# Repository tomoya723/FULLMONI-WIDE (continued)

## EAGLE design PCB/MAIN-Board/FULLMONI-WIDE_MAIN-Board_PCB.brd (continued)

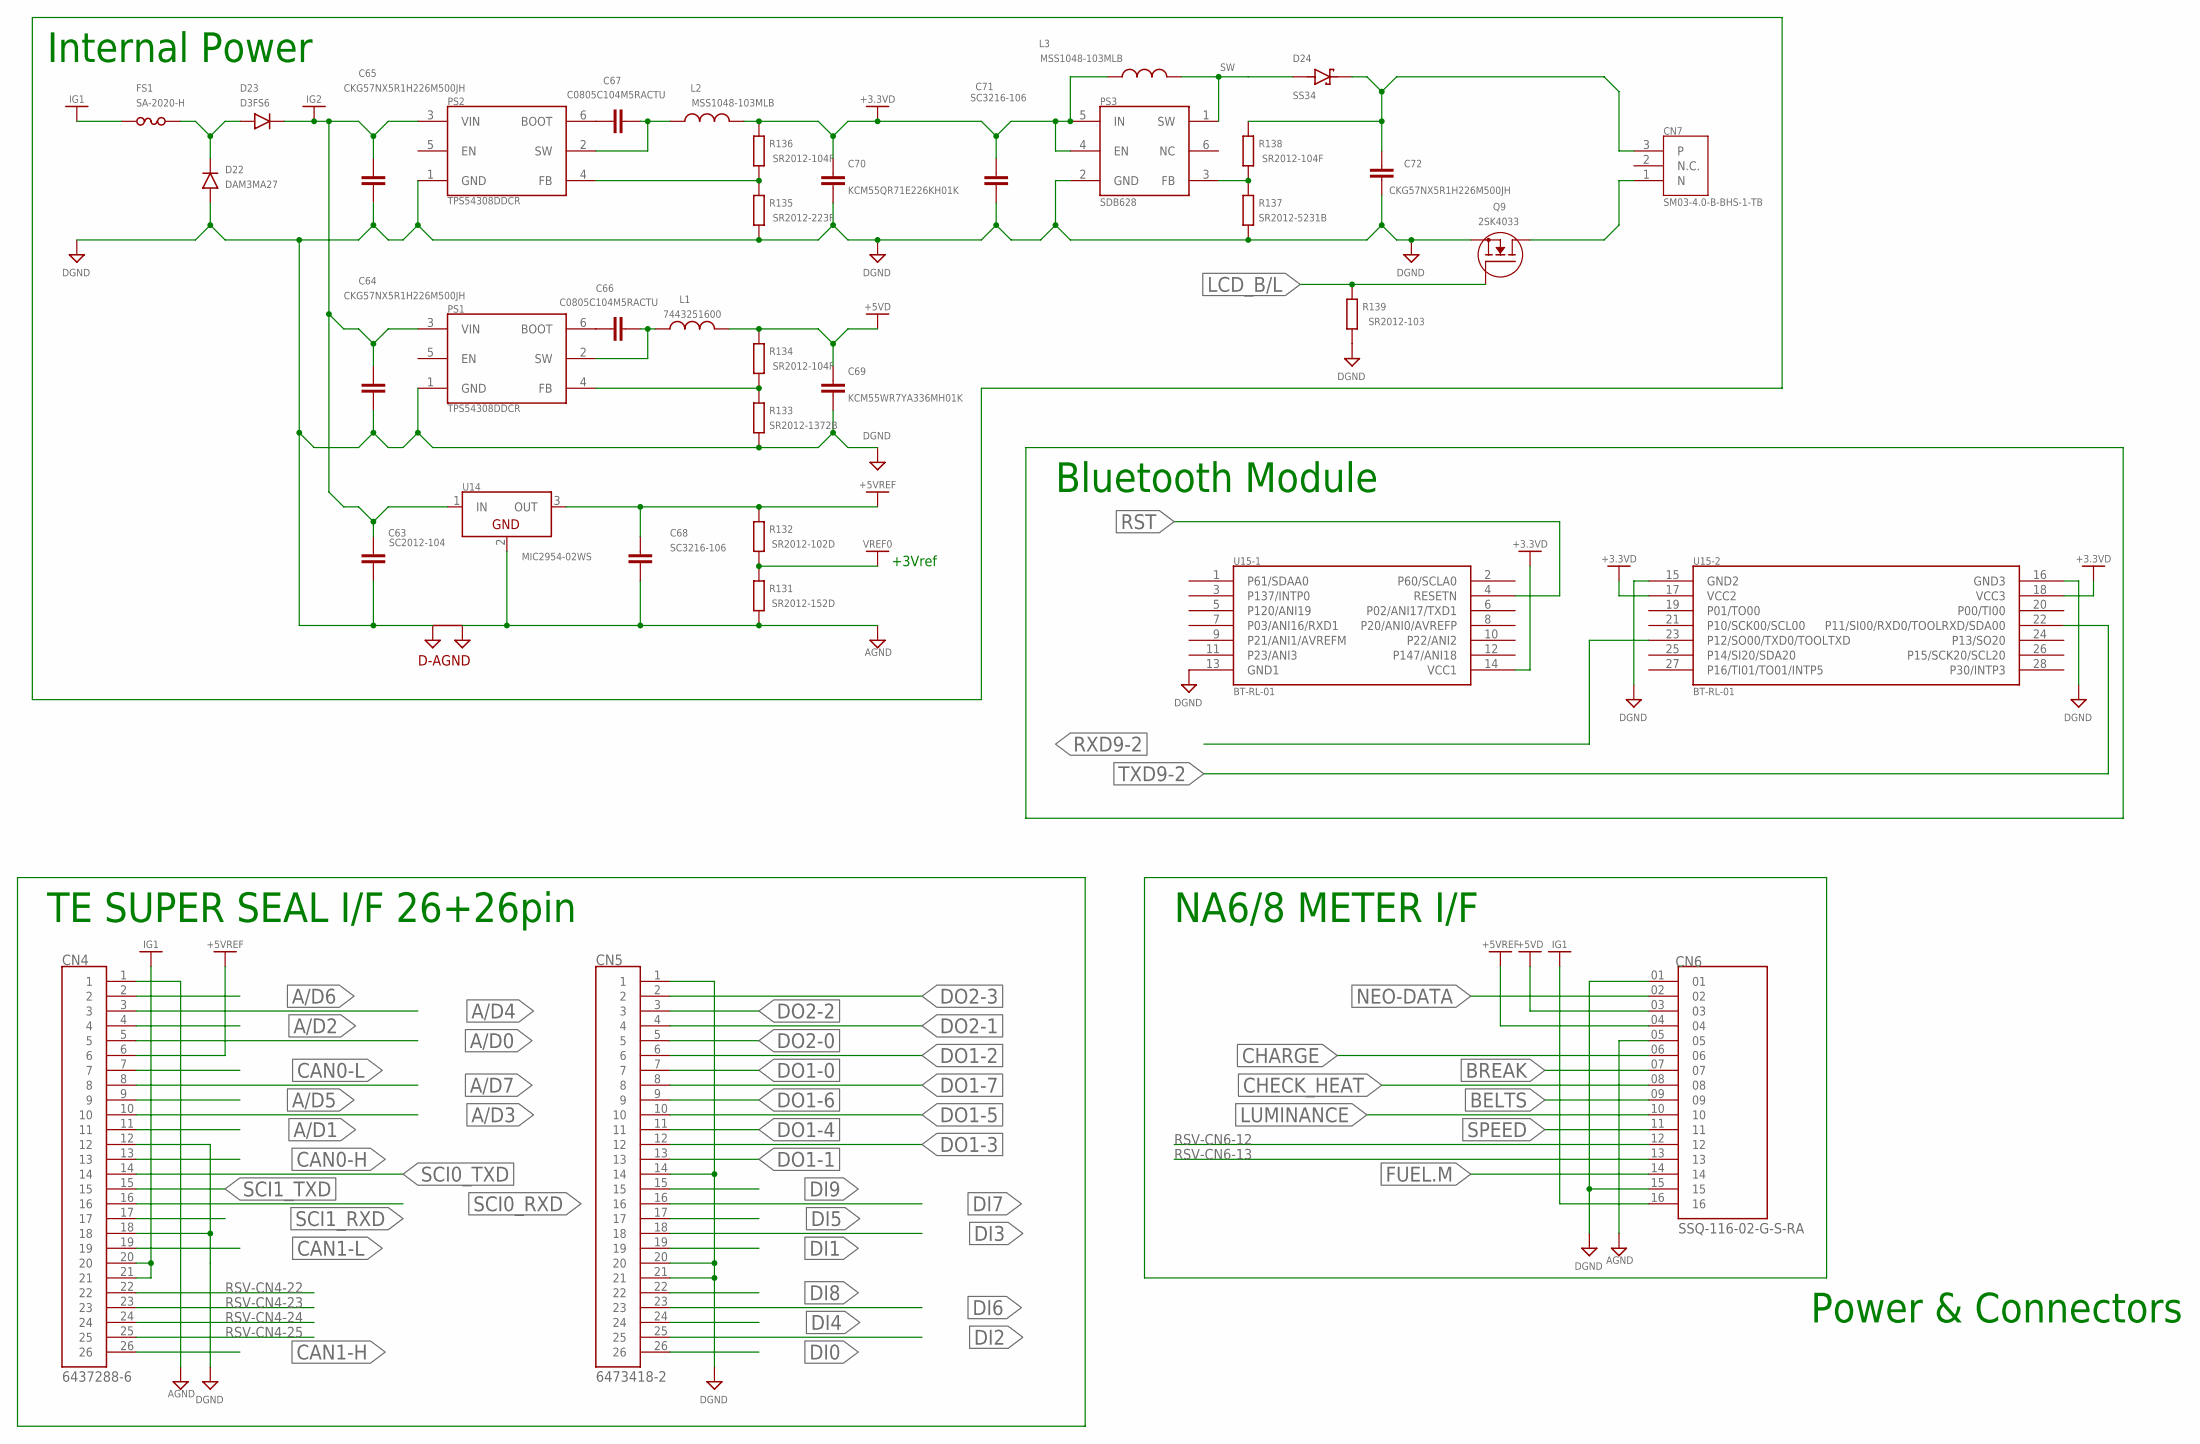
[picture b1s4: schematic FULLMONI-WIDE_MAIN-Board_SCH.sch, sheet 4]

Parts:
$4_490_$_2024-03-09_15-35-59: D-AGND
C63: SC2012-104; CAPC2012X110
C64, C65, C72: CKG57NX5R1H226M500JH
C66, C67: C0805C104M5RACTU; CAPC2012X110
C68, C71: SC3216-106; CAPC3216X135
C69: KCM55WR7YA336MH01K; KCM55QR71E226KH01K
C70: KCM55QR71E226KH01K
CN4: 6437288-6; TE_6437288-6
CN5: 6473418-2; TE_6473418-2
CN6: SSQ-116-02-G-S-RA; SAMTEC_SSQ-116-02-G-S-RA
CN7: SM03-4.0-B-BHS-1-TB
D22: DAM3MA27
D23: D3FS6
D24: SS34; DIOM6859X262N
FS1: SA-2020-H
L1: 7443251600; MSS1048-103MLB
L2, L3: MSS1048-103MLB
PS1, PS2: TPS54308DDCR; DBV_R-PDSO-G6
PS3: SDB628; TSOT23-6_DDC
Q9: 2SK4033; RJF0604JPD
R131: SR2012-152D; RESC2012X65
R132: SR2012-102D; RESC2012X65
R133: SR2012-1372B; RESC2012X65
R134, R136, R138: SR2012-104F; RESC2012X65
R135: SR2012-223F; RESC2012X65
R137: SR2012-5231B; RESC2012X65
R139: SR2012-103; RESC2012X65
U14: MIC2954-02WS
U15: BT-RL-01

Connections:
+3.3VD: C70.P$1, C71.1, L2.P$2 (2), L3.P$1 (1), PS3.4 (EN), PS3.5 (IN), R136.2, U15.14 (VCC1), U15.17 (VCC2), U15.18 (VCC3); also elsewhere on the board
+5VD: C69.P$1, CN6.03, L1.P$2 (2), R134.2; also elsewhere on the board
+5VREF: C68.1, CN4.6, CN6.04, R132.2, U14.3 (OUT); also elsewhere on the board
A/D0: CN4.5; also elsewhere on the board
A/D1: CN4.11; also elsewhere on the board
A/D2: CN4.4; also elsewhere on the board
A/D3: CN4.10; also elsewhere on the board
A/D4: CN4.3; also elsewhere on the board
A/D5: CN4.9; also elsewhere on the board
A/D6: CN4.2; also elsewhere on the board
A/D7: CN4.8; also elsewhere on the board
AGND: $4_490_$_2024-03-09_15-35-59.2 (AGND), C68.2, CN4.1, CN6.05, R131.1, U14.2 (GND); also elsewhere on the board
BELTS: CN6.09; also elsewhere on the board
BREAK: CN6.07; also elsewhere on the board
CAN0-H: CN4.13; also elsewhere on the board
CAN0-L: CN4.7; also elsewhere on the board
CAN1-H: CN4.26; also elsewhere on the board
CAN1-L: CN4.19; also elsewhere on the board
CHARGE: CN6.06; also elsewhere on the board
CHECK_HEAT: CN6.08; also elsewhere on the board
DGND: $4_490_$_2024-03-09_15-35-59.1 (DGND), C63.2, C64.P$2, C65.P$2, C69.P$2, C70.P$2, C71.2, C72.P$1, CN4.12, CN4.18, CN5.1, CN5.14, CN5.20, CN5.21, CN6.01, CN6.15, D22.P$1, PS1.1 (GND), PS2.1 (GND), PS3.2 (GND), Q9.3 (S), R133.1, R135.1, R137.1, R139.1, U15.13 (GND1), U15.15 (GND2), U15.16 (GND3); also elsewhere on the board
DI0: CN5.26; also elsewhere on the board
DI1: CN5.19; also elsewhere on the board
DI2: CN5.25; also elsewhere on the board
DI3: CN5.18; also elsewhere on the board
DI4: CN5.24; also elsewhere on the board
DI5: CN5.17; also elsewhere on the board
DI6: CN5.23; also elsewhere on the board
DI7: CN5.16; also elsewhere on the board
DI8: CN5.22; also elsewhere on the board
DI9: CN5.15; also elsewhere on the board
DO1-0: CN5.7; also elsewhere on the board
DO1-1: CN5.13; also elsewhere on the board
DO1-2: CN5.6; also elsewhere on the board
DO1-3: CN5.12; also elsewhere on the board
DO1-4: CN5.11; also elsewhere on the board
DO1-5: CN5.10; also elsewhere on the board
DO1-6: CN5.9; also elsewhere on the board
DO1-7: CN5.8; also elsewhere on the board
DO2-0: CN5.5; also elsewhere on the board
DO2-1: CN5.4; also elsewhere on the board
DO2-2: CN5.3; also elsewhere on the board
DO2-3: CN5.2; also elsewhere on the board
FUEL.M: CN6.14; also elsewhere on the board
IG1: CN4.20, CN4.21, CN6.16, FS1.2; also elsewhere on the board
IG2: C63.1, C64.P$1, C65.P$1, D23.P$2, PS1.3 (VIN), PS2.3 (VIN), U14.1 (IN)
LCD-A: C72.P$2, CN7.3, D24.C (K), R138.2
LCD-K: CN7.1 (N), Q9.4 (D)
LCD_B/L: Q9.1 (G), R139.2; also elsewhere on the board
LUMINANCE: CN6.10; also elsewhere on the board
unnamed: D22.P$2, D23.P$1, FS1.1
unnamed: C67.2, PS2.6 (BOOT)
unnamed: C66.2, PS1.6 (BOOT)
unnamed: C67.1, L2.P$1 (1), PS2.2 (SW)
unnamed: C66.1, L1.P$1 (1), PS1.2 (SW)
unnamed: PS2.4 (FB), R135.2, R136.1
unnamed: PS1.4 (FB), R133.2, R134.1
unnamed: PS3.3 (FB), R137.2, R138.1
NEO-DATA: CN6.02; also elsewhere on the board
RST: U15.4 (RESETN); also elsewhere on the board
RSV-CN4-22: CN4.22
RSV-CN4-23: CN4.23
RSV-CN4-24: CN4.24
RSV-CN4-25: CN4.25
RSV-CN6-12: CN6.12
RSV-CN6-13: CN6.13
RXD9-2: U15.23 (P12/SO00/TXD0/TOOLTXD); also elsewhere on the board
SCI0_RXD: CN4.16; also elsewhere on the board
SCI0_TXD: CN4.14; also elsewhere on the board
SCI1_RXD: CN4.17; also elsewhere on the board
SCI1_TXD: CN4.15; also elsewhere on the board
SPEED: CN6.11; also elsewhere on the board
SW: D24.A, L3.P$2 (2), PS3.1 (SW)
TXD9-2: U15.22 (P11/SI00/RXD0/TOOLRXD/SDA00); also elsewhere on the board
VREF0: R131.2, R132.1; also elsewhere on the board

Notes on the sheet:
Power & Connectors
+3Vref
TE SUPER SEAL I/F 26+26pin
NA6/8 METER I/F
Internal Power
Bluetooth Module

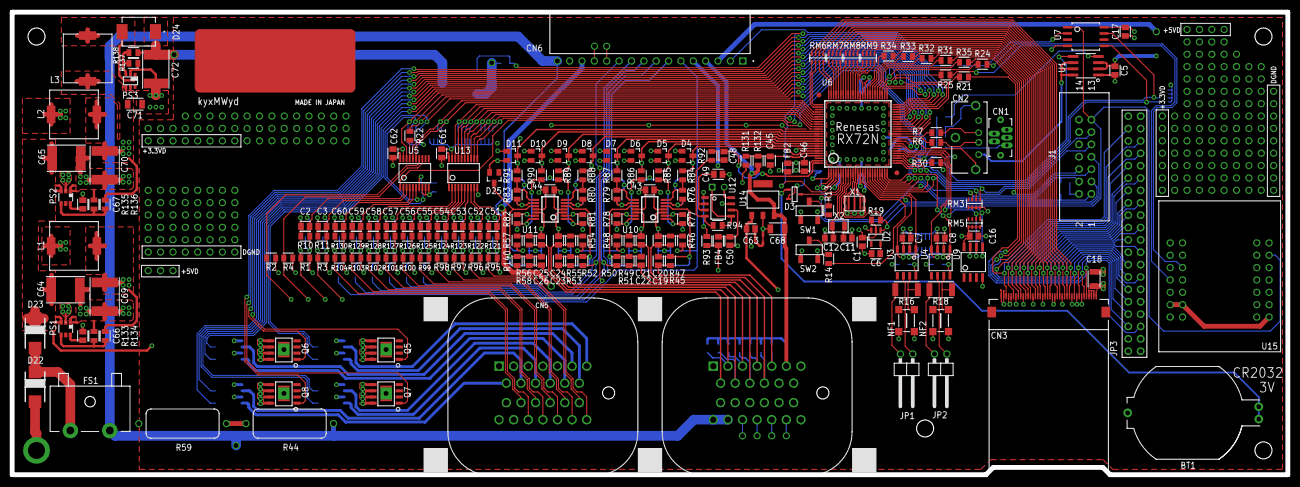
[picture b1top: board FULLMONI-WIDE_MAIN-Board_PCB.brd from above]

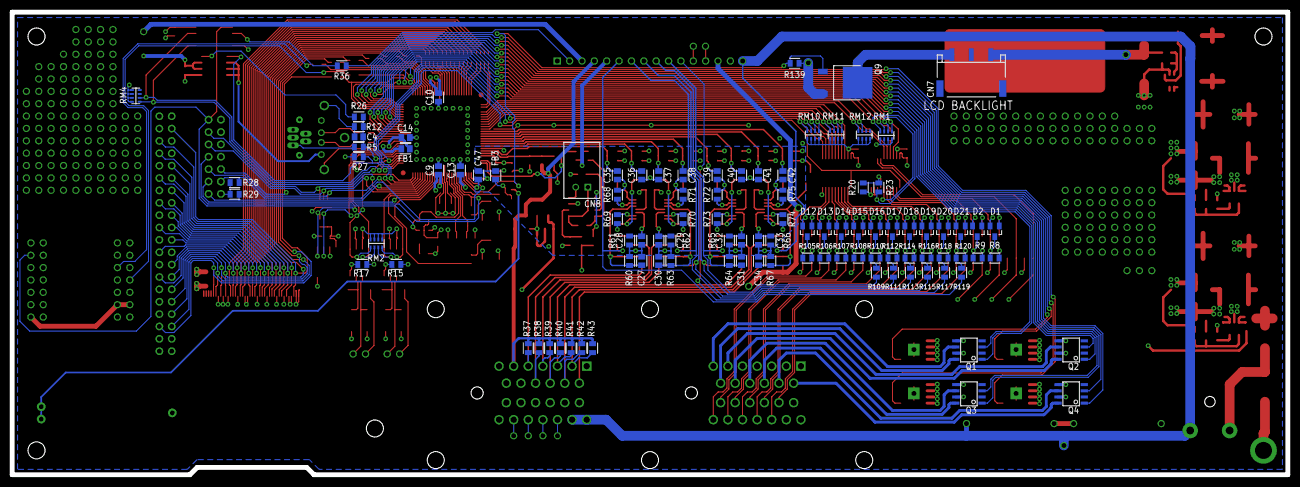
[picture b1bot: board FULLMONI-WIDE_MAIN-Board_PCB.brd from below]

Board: 4 copper layers, 262.0 x 95.0 mm, 303 parts (102 on the bottom side), 242 nets.

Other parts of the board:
U$2: FM-LOGO2

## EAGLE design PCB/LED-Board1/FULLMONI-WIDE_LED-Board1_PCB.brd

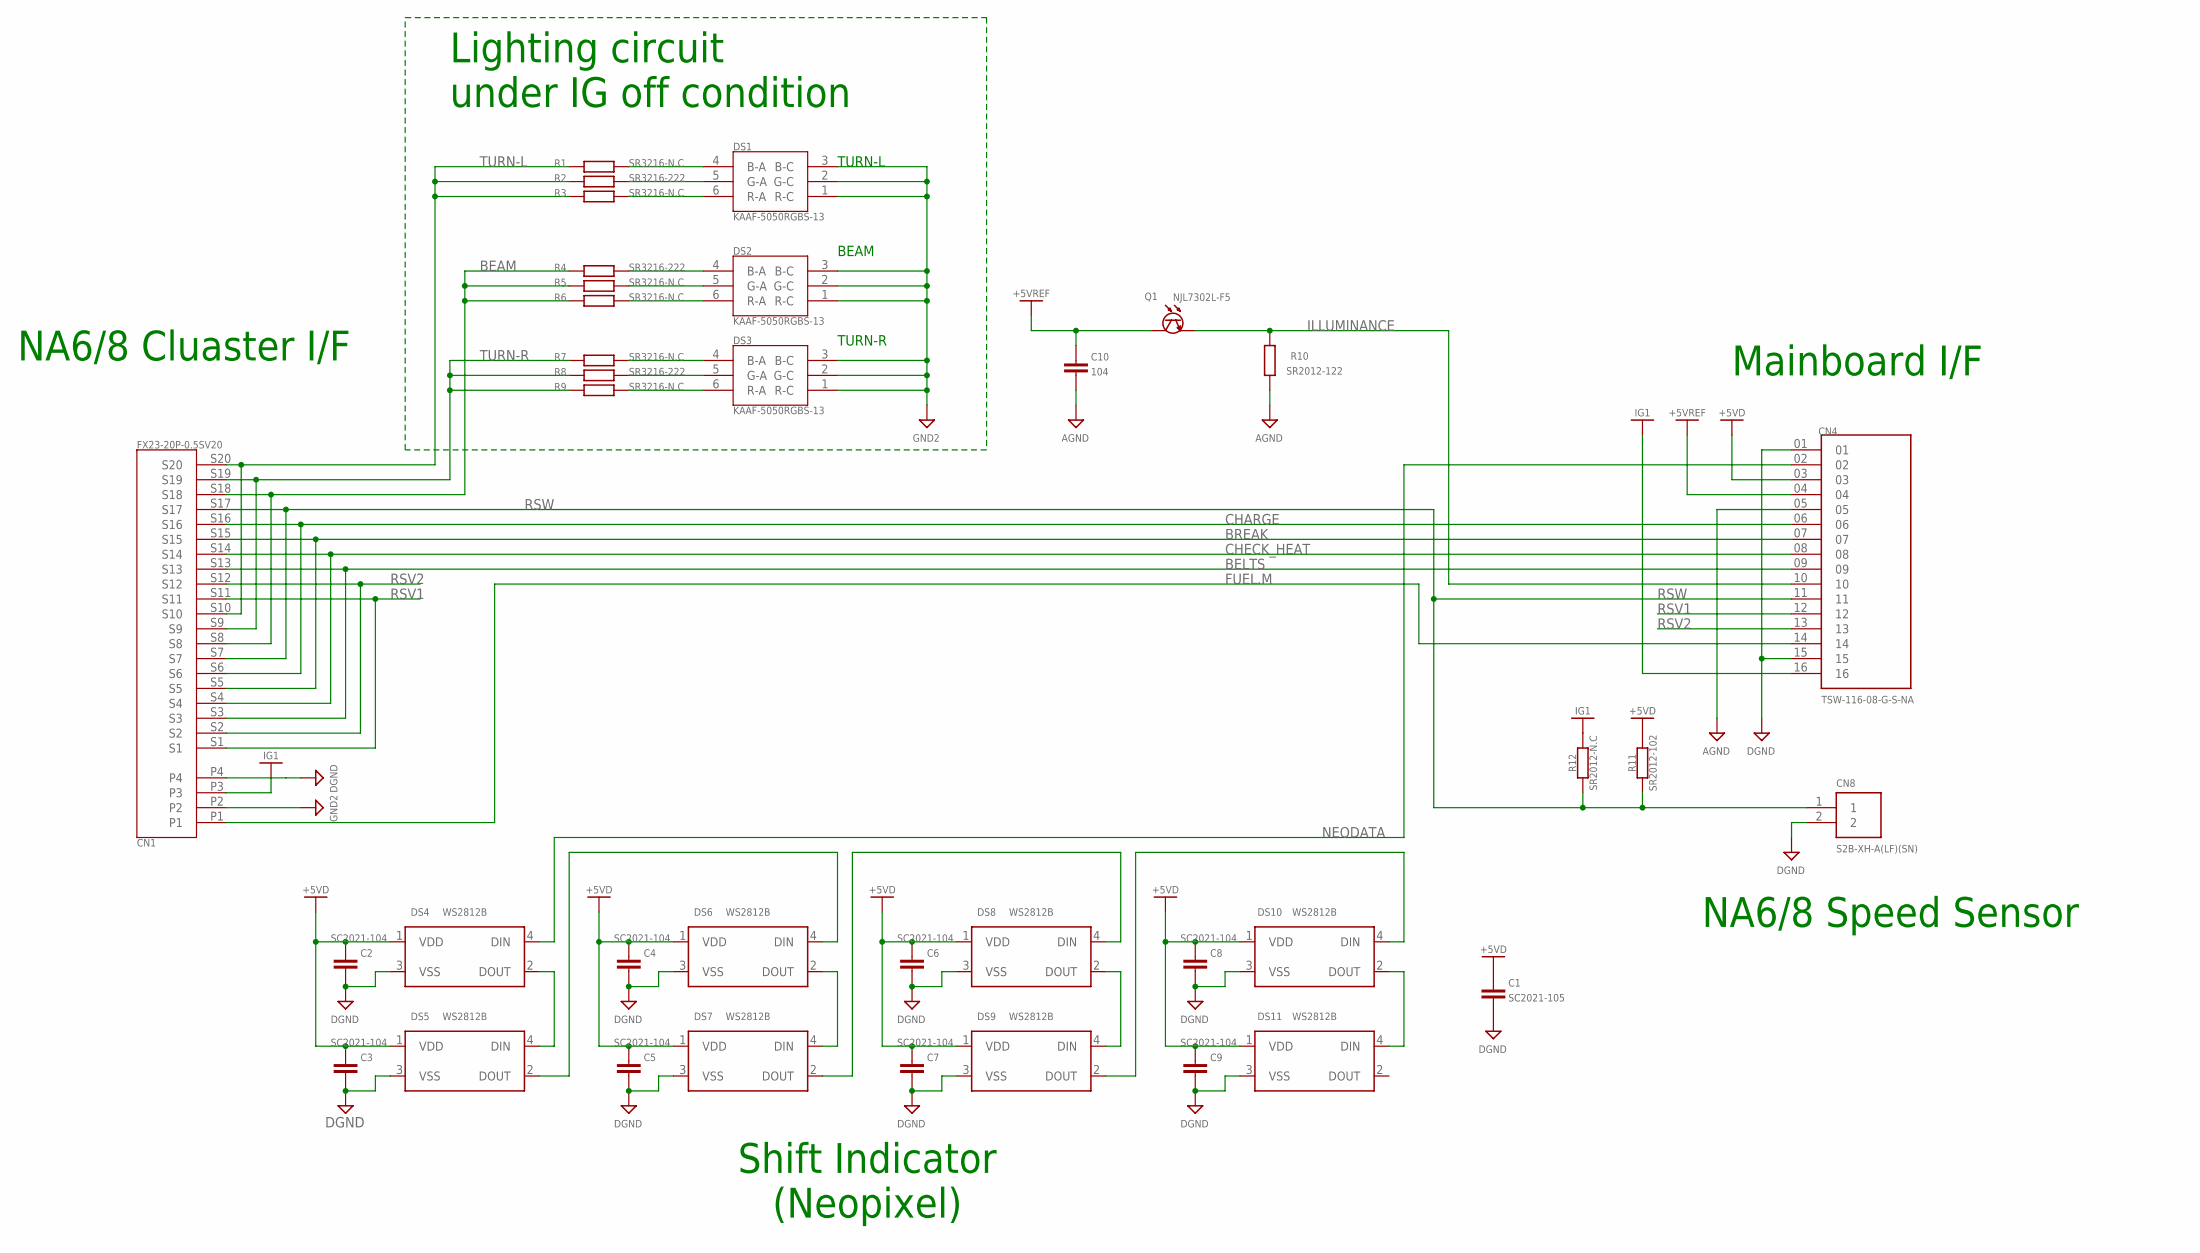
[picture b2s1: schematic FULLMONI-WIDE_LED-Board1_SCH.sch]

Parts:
C1: SC2021-105; CAPC3225X135
C2, C3, C4, C5, C6, C7, C8, C9: SC2021-104; CAPC2012X110
C10: 104; CAPC2012X110
CN1: FX23-20P-0.5SV20
CN4: TSW-116-08-G-S-NA; SAMTEC_TSW-116-08-G-S-NA
CN8: S2B-XH-A(LF)(SN); HDR-02/RA
DS1, DS2, DS3: KAAF-5050RGBS-13
DS4, DS5, DS6, DS7, DS8, DS9, DS10, DS11: WS2812B
Q1: NJL7302L-F5
R1, R3, R5, R6, R7, R9: SR3216-N.C; R3216
R2, R4, R8: SR3216-222; R3216
R10: SR2012-122; RESC2012X65
R11: SR2012-102; RESC2012X65
R12: SR2012-N.C; RESC2012X65

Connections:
+5VD: C1.1, C2.1, C3.1, C4.1, C5.1, C6.1, C7.1, C8.1, C9.1, CN4.03, DS4.1 (VDD), DS5.1 (VDD), DS6.1 (VDD), DS7.1 (VDD), DS8.1 (VDD), DS9.1 (VDD), DS10.1 (VDD), DS11.1 (VDD), R11.2
+5VREF: C10.1, CN4.04, Q1.P$2 (C)
AGND: C10.2, CN4.05, R10.1
BEAM: CN1.S8, CN1.S18, R4.1, R5.1, R6.1
BELTS: CN1.S3, CN1.S13, CN4.09
BREAK: CN1.S5, CN1.S15, CN4.07
CHARGE: CN1.S6, CN1.S16, CN4.06
CHECK_HEAT: CN1.S4, CN1.S14, CN4.08
DGND: C1.2, C2.2, C3.2, C4.2, C5.2, C6.2, C7.2, C8.2, C9.2, CN1.P4, CN4.01, CN4.15, CN8.2, DS4.3 (VSS), DS5.3 (VSS), DS6.3 (VSS), DS7.3 (VSS), DS8.3 (VSS), DS9.3 (VSS), DS10.3 (VSS), DS11.3 (VSS)
FUEL.M: CN1.P1, CN4.14
GND2: CN1.P2, DS1.1 (R-C), DS1.2 (G-C), DS1.3 (B-C), DS2.1 (R-C), DS2.2 (G-C), DS2.3 (B-C), DS3.1 (R-C), DS3.2 (G-C), DS3.3 (B-C)
IG1: CN1.P3, CN4.16, R12.2
ILLUMINANCE: CN4.10, Q1.P$1 (E), R10.2
unnamed: DS1.4 (B-A), R1.2
unnamed: DS3.4 (B-A), R7.2
unnamed: DS2.4 (B-A), R4.2
unnamed: DS1.5 (G-A), R2.2
unnamed: DS1.6 (R-A), R3.2
unnamed: DS3.5 (G-A), R8.2
unnamed: DS3.6 (R-A), R9.2
unnamed: DS2.5 (G-A), R5.2
unnamed: DS2.6 (R-A), R6.2
unnamed: DS4.2 (DOUT), DS5.4 (DIN)
unnamed: DS5.2 (DOUT), DS6.4 (DIN)
unnamed: DS6.2 (DOUT), DS7.4 (DIN)
unnamed: DS7.2 (DOUT), DS8.4 (DIN)
unnamed: DS8.2 (DOUT), DS9.4 (DIN)
unnamed: DS9.2 (DOUT), DS10.4 (DIN)
unnamed: DS10.2 (DOUT), DS11.4 (DIN)
NEODATA: CN4.02, DS4.4 (DIN)
RSV1: CN1.S1, CN1.S11, CN4.12
RSV2: CN1.S2, CN1.S12, CN4.13
RSW: CN1.S7, CN1.S17, CN4.11, CN8.1, R11.1, R12.1
TURN-L: CN1.S10, CN1.S20, R1.1, R2.1, R3.1
TURN-R: CN1.S9, CN1.S19, R7.1, R8.1, R9.1

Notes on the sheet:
Lighting circuit under IG off condition
TURN-L
TURN-R
BEAM
NA6/8 Speed Sensor
Mainboard I/F
NA6/8 Cluaster I/F
Shift Indicator (Neopixel)

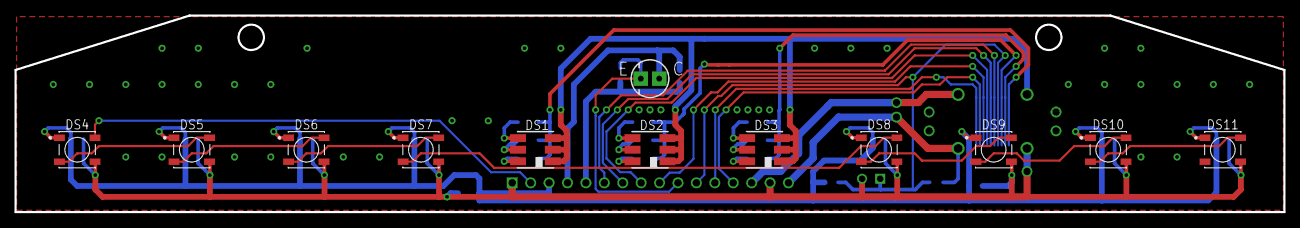
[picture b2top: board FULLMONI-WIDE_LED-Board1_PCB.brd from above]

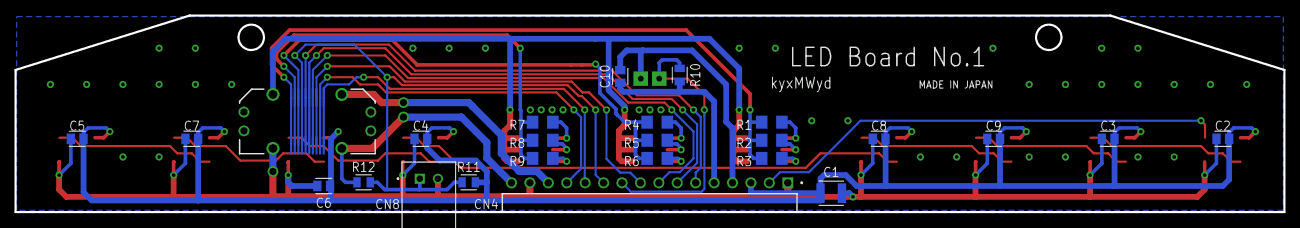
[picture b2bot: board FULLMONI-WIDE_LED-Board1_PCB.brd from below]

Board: 2 copper layers, 175.0 x 27.1 mm, 37 parts (25 on the bottom side), 35 nets.

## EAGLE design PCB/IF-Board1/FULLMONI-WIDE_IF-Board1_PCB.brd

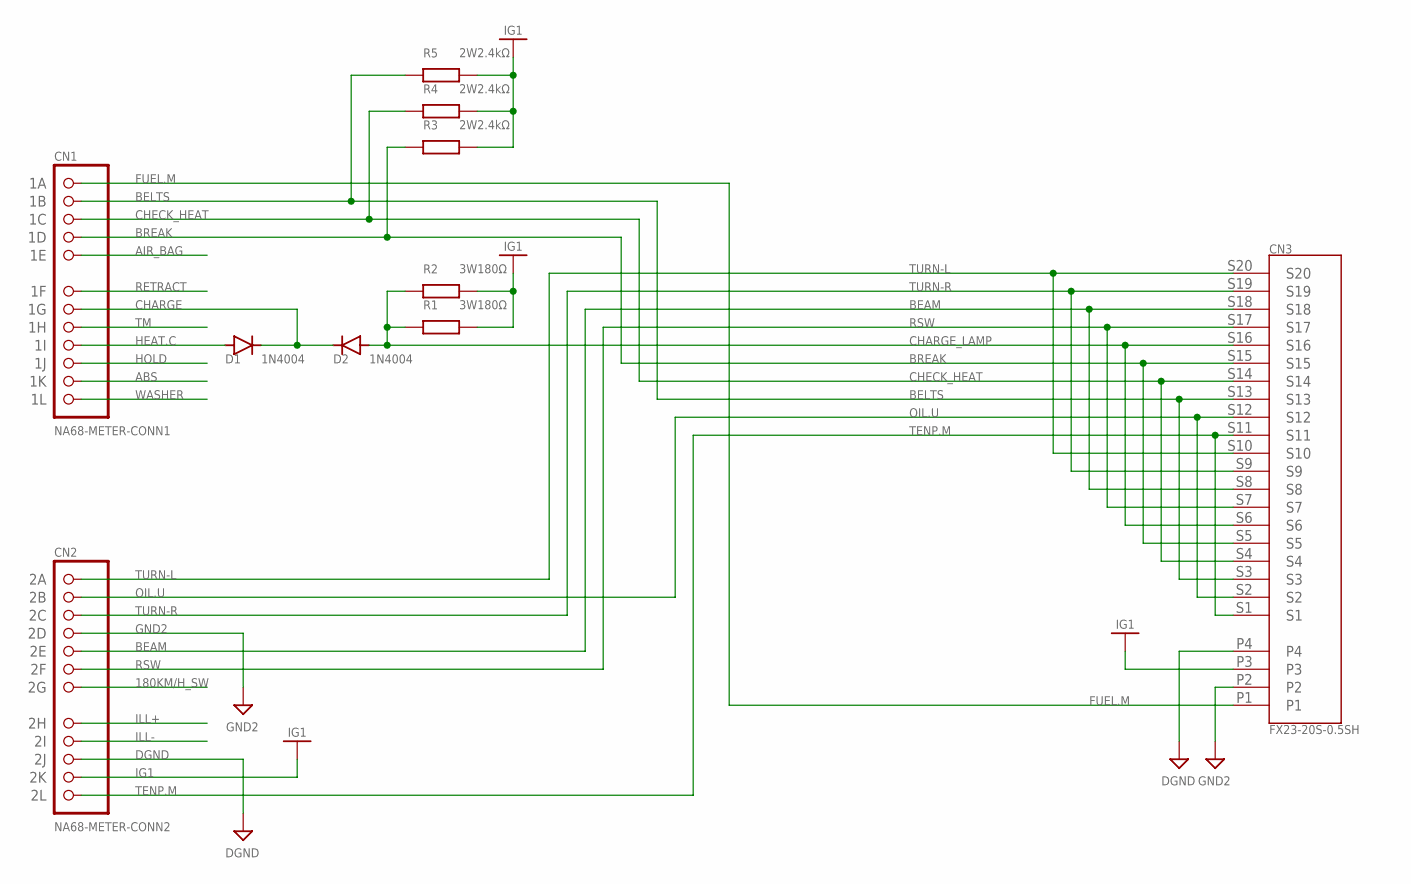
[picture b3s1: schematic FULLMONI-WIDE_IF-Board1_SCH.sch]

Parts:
CN1: NA68-METER-CONN1
CN2: NA68-METER-CONN2
CN3: FX23-20S-0.5SH
D1, D2: 1N4004; DO41-10
R1, R2: 3W180Ω; 0617/17
R3, R4, R5: 2W2.4kΩ; RLF2SJ

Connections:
180KM/H_SW: CN2.P$7 (2G)
ABS: CN1.P$11 (1K)
AIR_BAG: CN1.P$5 (1E)
BEAM: CN2.P$5 (2E), CN3.S8, CN3.S18
BELTS: CN1.P$2 (1B), CN3.S3, CN3.S13, R5.1
BREAK: CN1.P$4 (1D), CN3.S5, CN3.S15, R3.1
CHARGE: CN1.P$7 (1G), D1.C, D2.C
CHARGE_LAMP: CN3.S6, CN3.S16, D2.A, R1.1, R2.1
CHECK_HEAT: CN1.P$3 (1C), CN3.S4, CN3.S14, R4.1
DGND: CN2.P$10 (2J), CN3.P4
FUEL.M: CN1.P$1 (1A), CN3.P1
GND2: CN2.P$4 (2D), CN3.P2
HEAT.C: CN1.P$9 (1I), D1.A
HOLD: CN1.P$10 (1J)
IG1: CN2.P$11 (2K), CN3.P3, R1.2, R2.2, R3.2, R4.2, R5.2
ILL+: CN2.P$8 (2H)
ILL-: CN2.P$9 (2I)
OIL.U: CN2.P$2 (2B), CN3.S2, CN3.S12
RETRACT: CN1.P$6 (1F)
RSW: CN2.P$6 (2F), CN3.S7, CN3.S17
TENP.M: CN2.P$12 (2L), CN3.S1, CN3.S11
TM: CN1.P$8 (1H)
TURN-L: CN2.P$1 (2A), CN3.S10, CN3.S20
TURN-R: CN2.P$3 (2C), CN3.S9, CN3.S19
WASHER: CN1.P$12 (1L)

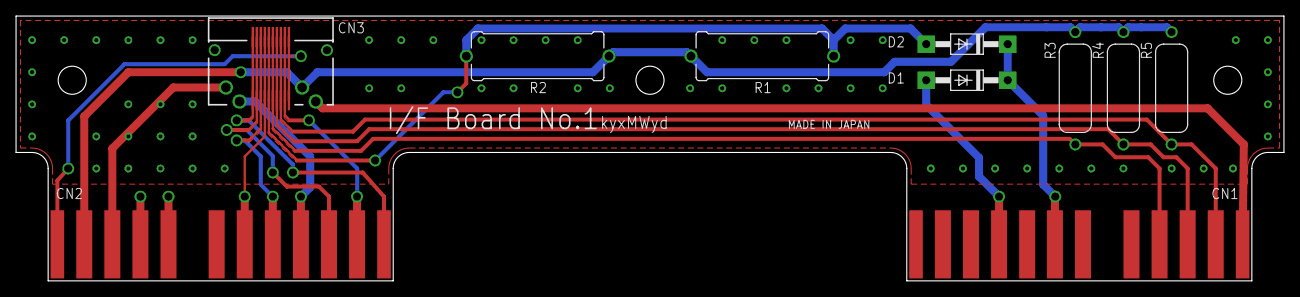
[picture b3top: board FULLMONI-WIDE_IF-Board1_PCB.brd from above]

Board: 2 copper layers, 158.0 x 33.0 mm, 10 parts (0 on the bottom side), 16 nets.

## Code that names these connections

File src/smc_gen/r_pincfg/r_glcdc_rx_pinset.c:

/***********************************************************************************************************************
* DISCLAIMER
* This software is supplied by Renesas Electronics Corporation and is only intended for use with Renesas products.
* No other uses are authorized. This software is owned by Renesas Electronics Corporation and is protected under all
* applicable laws, including copyright laws. 
* THIS SOFTWARE IS PROVIDED "AS IS" AND RENESAS MAKES NO WARRANTIES REGARDING THIS SOFTWARE, WHETHER EXPRESS, IMPLIED
* OR STATUTORY, INCLUDING BUT NOT LIMITED TO WARRANTIES OF MERCHANTABILITY, FITNESS FOR A PARTICULAR PURPOSE AND
* NON-INFRINGEMENT.  ALL SUCH WARRANTIES ARE EXPRESSLY DISCLAIMED.TO THE MAXIMUM EXTENT PERMITTED NOT PROHIBITED BY
* LAW, NEITHER RENESAS ELECTRONICS CORPORATION NOR ANY OF ITS AFFILIATED COMPANIES SHALL BE LIABLE FOR ANY DIRECT,
* INDIRECT, SPECIAL, INCIDENTAL OR CONSEQUENTIAL DAMAGES FOR ANY REASON RELATED TO THIS SOFTWARE, EVEN IF RENESAS OR
* ITS AFFILIATES HAVE BEEN ADVISED OF THE POSSIBILITY OF SUCH DAMAGES.
* Renesas reserves the right, without notice, to make changes to this software and to discontinue the availability 
* of this software. By using this software, you agree to the additional terms and conditions found by accessing the 
* following link:
* http://www.renesas.com/disclaimer
*
* Copyright (C) 2024 Renesas Electronics Corporation. All rights reserved.
***********************************************************************************************************************/
/***********************************************************************************************************************
* File Name    : r_glcdc_rx_pinset.c
* Version      : 1.0.2
* Device(s)    : R5F572NNDxFP
* Tool-Chain   : RXC toolchain
* Description  : Setting of port and mpc registers
***********************************************************************************************************************/

/***********************************************************************************************************************
Includes
***********************************************************************************************************************/
#include "r_glcdc_rx_pinset.h"
#include "platform.h"

/***********************************************************************************************************************
Global variables and functions
***********************************************************************************************************************/
/***********************************************************************************************************************
* Function Name: R_GLCDC_PinSet
* Description  : This function initializes pins for r_glcdc_rx module
* Arguments    : none
* Return Value : none
***********************************************************************************************************************/
void R_GLCDC_PinSet()
{
    R_BSP_RegisterProtectDisable(BSP_REG_PROTECT_MPC);

    /* Set LCD_CLK pin */
    MPC.PB5PFS.BYTE = 0x25U;
    PORTB.PMR.BIT.B5 = 1U;

    /* Set LCD_TCON2 pin */
    MPC.PB2PFS.BYTE = 0x25U;
    PORTB.PMR.BIT.B2 = 1U;

    /* Set LCD_DATA0 pin */
    MPC.PB0PFS.BYTE = 0x25U;
    PORTB.PMR.BIT.B0 = 1U;

    /* Set LCD_DATA1 pin */
    MPC.PA7PFS.BYTE = 0x25U;
    PORTA.PMR.BIT.B7 = 1U;

    /* Set LCD_DATA2 pin */
    MPC.PA6PFS.BYTE = 0x25U;
    PORTA.PMR.BIT.B6 = 1U;

    /* Set LCD_DATA3 pin */
    MPC.PA5PFS.BYTE = 0x25U;
    PORTA.PMR.BIT.B5 = 1U;

    /* Set LCD_DATA4 pin */
    MPC.PA4PFS.BYTE = 0x25U;
    PORTA.PMR.BIT.B4 = 1U;

    /* Set LCD_DATA5 pin */
    MPC.PA3PFS.BYTE = 0x25U;
    PORTA.PMR.BIT.B3 = 1U;

    /* Set LCD_DATA6 pin */
    MPC.PA2PFS.BYTE = 0x25U;
    PORTA.PMR.BIT.B2 = 1U;

    /* Set LCD_DATA7 pin */
    MPC.PA1PFS.BYTE = 0x25U;
    PORTA.PMR.BIT.B1 = 1U;

    /* Set LCD_DATA8 pin */
    MPC.PA0PFS.BYTE = 0x25U;
    PORTA.PMR.BIT.B0 = 1U;

    /* Set LCD_DATA9 pin */
    MPC.PE7PFS.BYTE = 0x25U;
    PORTE.PMR.BIT.B7 = 1U;

    /* Set LCD_DATA10 pin */
    MPC.PE6PFS.BYTE = 0x25U;
    PORTE.PMR.BIT.B6 = 1U;

    /* Set LCD_DATA11 pin */
    MPC.PE5PFS.BYTE = 0x25U;
    PORTE.PMR.BIT.B5 = 1U;

    /* Set LCD_DATA12 pin */
    MPC.PE4PFS.BYTE = 0x25U;
    PORTE.PMR.BIT.B4 = 1U;

    /* Set LCD_DATA13 pin */
    MPC.PE3PFS.BYTE = 0x25U;
    PORTE.PMR.BIT.B3 = 1U;

    /* Set LCD_DATA14 pin */
    MPC.PE2PFS.BYTE = 0x25U;
    PORTE.PMR.BIT.B2 = 1U;

    /* Set LCD_DATA15 pin */
    MPC.PE1PFS.BYTE = 0x25U;
    PORTE.PMR.BIT.B1 = 1U;

    R_BSP_RegisterProtectEnable(BSP_REG_PROTECT_MPC);
}

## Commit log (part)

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2025-03-17 update v0.0.4 bugfix
2025-03-24 bugfix issue#4 & issue#7 & issue#9. patch issue#8.
2025-03-27 add guard / smoothing library add smoothing to MAP / OilPressure
2025-03-30 Update README.md CAN data description
2025-03-30 Update README.md
    node simulation usage added
2025-04-05 Update issue templates
2025-08-19 Update LICENSE
2025-08-28 nodesim rev step up
2026-01-02 Fix issue#33: 油圧表示桁あふれの対策
    油圧計算の係数を0.1から0.001に変更し、表示側で100することで、
    3桁表示のまま最大999100=99900kPaまで対応可能にした。
    - 油圧計算係数: 0.1 0.001
    - CANデータ値 0.001 = 内部値（1/100）
    - 内部値 100 = 表示値（正しいkPa値）
    Closes #33
2026-01-04 feat: Add S7 record length validation - Fix false S7 detection at 0msec/line transfer (5min for 76K lines)
2026-01-05 fix(bootloader): ブートローダ起動アプリ起動、ファイル転送成功
    - BL_APP_STARTを0xFFC40000から0xFFC20000に修正（アプリの.text開始アドレスと一致）
    - exec_image()でPowerON_Resetに直接ジャンプするように修正
    - ブートローダ128KB、アプリ3.875MBのメモリマップに更新
    - 液晶表示含むアプリケーションの正常起動を確認
2026-01-05 perf(bootloader): reduce XOFF wait time from 5ms to 2ms
    - Transfer time reduced from 2m40s to ~2m (25% faster)
    - Add initial XON send before waiting for data
    - Total optimization: 10min -> 2min (80% faster than original)
2026-01-05 chore: remove scfg file and add warning to README
    - Delete Bootloader.scfg to prevent accidental Smart Configurator regeneration
    - Add warning to README about not using Smart Configurator
    - r_Config_SCI9_receive_interrupt() has custom implementation that would be overwritten
2026-01-06 feat: add parameter console via SCI9 UART
    - Add param_storage.h/c: EEPROM parameter management with CRC
    - Add param_console.h/c: UART terminal console with command parser
    - Add MODE_NORMAL/MODE_PARAM system mode switching
    - Support commands: help, list, set, save, load, default
    - Support RTC commands: rtc (show/set YY MM DD hh mm ss)
    - Support ODO commands: odo, odo_init <km>
2026-01-06 feat: Add fwupdate command for UART firmware update
    - Add fwupdate command in param_console.c
    - Sets magic number (0xDEADBEEF) at RAM2 (0x0087FFF0)
    - Triggers software reset to bootloader
    - Requires 'yes' confirmation with 10s timeout
    - Bootloader enhancements (boot_loader.c/h):
    - Check force update flag from RAM2 on startup
2026-01-06 fix: SCI9受信割り込みで継続受信を有効化
    - r_Config_SCI9_receive_interrupt()で受信後にRE/RIEビットを再設定
    - r_Config_SCI9_receiveerror_interrupt()でエラー後も受信を継続
    - ターミナルキー入力が1回で停止する問題を修正
2026-01-07 refactor: rename FullmoniTerminal to FULLMONI-WIDE-Terminal
    - Rename folder: FullmoniTerminal -> FULLMONI-WIDE-Terminal
    - Rename project files: *.csproj, *.sln
    - Update window title to 'FULLMONI-WIDE Terminal'
    - Update AssemblyName and Product in csproj
    - Update documentation paths in README.md
    - Add input validation for all parameters
2026-01-10 feat: Add USB PCDC integration for Bootloader
    - Add r_usb_basic FIT module v1.44 to Bootloader and Firmware
    - Add r_usb_pcdc FIT module v1.44 for CDC class support
    - Create main_fit_cdc.c for USB CDC communication in Bootloader
    - Add USB descriptors for CDC device enumeration
    - Fix CDC class request handling (SET_LINE_CODING, GET_LINE_CODING)
    - Use R_USB_Read/Write APIs based on official Renesas sample
2026-01-11 feat: ファームウェア転送速度を175倍高速化 (10秒で1.2MB転送)
    - Bootloader: ACK間隔を128バイト4KB(ACK_INTERVAL_BYTES)に変更
    - WinApp: チャンクサイズを64512バイトに変更
    - WinApp: XON/XOFFフロー制御を無効化(主因)
    - WinApp: シリアルバッファを8KBに拡大
    - WinApp: UIフリーズ対策(Task.Yield追加)
2026-01-11 chore: デバッグコード削除、fwupdate時のLCD FadeOUT追加、更新後の自動再接続
    - param_console.c: DEBUGログ削除、fwupdateでLCD_FadeOUT()追加
    - FirmwareUpdateService.cs: DEBUGログ削除
    - MainViewModel.cs: ファームウェア更新完了後に自動で切断再接続
2026-01-11 docs: README.md を最新仕様に更新
    - 技術スタック: USB CDC、VS Code、ホストアプリ追加
    - ディレクトリ構成: Bootloader, HostApp, docs追加
    - 主要機能: USB CDCファームウェア更新、パラメータコンソール追加
    - ホストアプリケーション セクション新設
    - ロードマップ: ユーザリプロ対応、ドキュメント拡充を完了
2026-01-11 Add implementation summary document
    - Created IMPLEMENTATION_SUMMARY.md with complete overview
    - Documents all changes, design decisions, and usage
    - Includes compatibility and testing information
2026-01-11 Fix image preview visibility and update documentation for startup image feature
2026-01-13 feat: 起動画面読み書き機能 (imgread/imgwrite) を実装
    - imgwriteコマンド: BMPをAppWizard形式に変換しフラッシュに書き込み
    - imgreadコマンド: フラッシュから起動画面を読み出し (2ms/64Bパケット遅延)
    - mtcinfoコマンド: acmtcシンボル情報表示
    - USB CDC: 送信専用制御構造体追加、ZLP送信、デバッグカウンタ
    - HostApp: SerialPortService直接読み取り、終端マーカー検出プロトコル
    - AppWizardImageConverter: BMPRGB565相互変換
2026-01-13 Add comprehensive documentation on emWin resource address behavior
2026-01-15 docs: 起動画像固定アドレス配置についてドキュメント追加
    - Firmware/README.md: リンカスクリプトによる固定配置の説明追加
    - HostApp README.md: ファームウェア更新後も画像保持される旨を追記
2026-01-15 ci: AppWizardリソースの簡易チェックを追加
    - 参照されている配列に対応するファイルが存在するかチェック
    - Image/Fontフォルダの未追跡ファイルを検出
    - 今回のようなAppWizard再生成不備を防止
2026-01-15 fix(eeprom): BR24A16F(24C16) EEPROM対応とCAN設定永続化 (#65)
    - EEPROM 24C16アドレッシング修正（1バイトアドレス、上位3ビットはI2Cアドレスに埋め込み）
    - ページサイズを3216バイトに修正
    - main.c ODO読み込みを1バイトアドレス形式に修正
    - CAN設定のEEPROM保存読み込み機能実装
    - SCI9デバッグ出力対応（printf経由）
    - HostApp CAN設定送信時に自動保存
2026-01-17 feat(speaker): 起動音と警告音のカスタムサウンド対応
    - 起動音にblip音（0.31秒）を追加
    - 警告音にビープ音（0.44秒）を追加（speaker_play_warning API）
    - PCMデータ用のヘッダーファイル生成スクリプト改善
    - 8bit PCM 12bit DAC変換の最適化
2026-01-17 feat(Issue #50): マスターワーニング機能の基本実装
    - CAN_Field_t構造体を拡張 (1230 bytes)
    - name[8]: パラメータ名 (警告表示用)
    - unit[4]: 単位文字列
    - warn_enabled: ワーニング有効フラグ
    - warn_low/warn_high: 閾値設定
    - CAN_CONFIG_VERSIONを2に更新
2026-01-18 feat(Issue #50): マスターワーニング機能実装 - GUIヒープ増加 (80KB110KB) - master_warning_check()にCAN設定有効性チェック追加 - ID_TEXT_ACCを警告表示に再利用 - メータ更新とマスターワーニング表示の両立
2026-01-23 chore(debug): nodesimのテスト値を調整
2026-01-23 feat: マスターワーニング発報中にシフトLEDを赤色明滅に変更
    - ワーニング発報中はシフトインジケータを中止
    - 8つのLED全て赤色でじわじわ明滅（3秒周期）
    - ワーニング解除後は通常のシフト表示に復帰
    TODO: Hi,Lo別にENを分ける
2026-01-25 feat(terminal): Modernize UI with WPF-UI Fluent Design
    - Replace custom styles with WPF-UI 4.2.0 Fluent Design components
    - Add graphical home page with hero banner and card navigation
    - Implement hero image slideshow (FM2/FM3 alternating every 5s)
    - Localize entire UI to English
    - Enhance About page with feature descriptions
    - Unify icons between sidebar and home page cards
2026-01-30 fix(OIL-P): divisor修正で表示値警告判定を正常化
    - param_storage.c: OIL-P divisor を 1000100 に変更
    - CAN値5000 内部値50 表示5.0 x100kPa
    - param_storage.h: CAN_CONFIG_VERSION を 78 に更新
    - EEPROM設定リセットでデフォルト値を適用
    - AppWizard: ID_NUM_05 桁数 34、ID_PROGBAR_OILP Range 80080
2026-02-01 chore: postbuildStepでFirmware_noofs.mot自動生成、中間ファイル削除
2026-02-01 feat: Junction-based variant switching for aw001/aw002
    - Changed all hardcoded ../aw002/ include paths to ../aw/ for Junction support
    - Fixed aw001 bugs: RTC stuck at 00:00 and missing green/red dialogs
    - Added switch_to_aw001.bat and switch_to_aw002.bat for easy variant switching
    - Updated build_variants.ps1 for automated both-variant builds
    - Updated Firmware/README.md and tools/README.md with Junction documentation
    - Modified e2 studio project settings to use aw/Resource and aw/Source
2026-02-01 Add capture_thumbnails.ps1 for automated thumbnail generation
    - Auto-detect aw001, aw002, ... variants (exclude 'aw' symlink)
    - Auto-copy GUI_Lib from AppWizard or backup
    - Auto-build GUISimulation.exe with MSBuild (SDK 10.0, v145)
    - Capture 800x256 LCD area with ForceSetForegroundWindow
    - Update .gitignore to exclude GUI_Lib, Exe, Output folders
    - Update release procedure documentation
2026-02-02 Add: リリース自動化スクリプト (release.ps1)
2026-02-03 docs(Android): Add TCP Bridge testing guide for emulator
2026-02-06 feat(Android): Add parameter validation - Add validation for tyre, gear ratio, warning, shift RPM settings - Check value ranges and relational constraints (same as Windows) - Show validation error di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
2026-02-06 chore: Remove FULLMONI-WIDE-Desktop (use com_bridge.ps1 instead)
2026-02-11 chore: add Git hooks to protect linker_script.ld from e2 studio corruption
2026-02-11 chore: add Git hooks to protect linker_script.ld from e2 studio corruption (#101)
2026-02-11 fix: CAN MKRレジスタ共有問題を修正
    問題: 無効チャンネルでマスク0x000を設定すると、MKRレジスタを共有する
    他の有効チャンネルのマスクも0x000になってしまう
    (MKR[2]はMailbox 8-11で共有: CANBOX_RX5, RX6)
    結果: CH6無効時にCH5のマスクも0x000になり、全CAN IDを受信
    → 0x3EC(車速)のMailboxに0x3ED(ギア)も混入、0km/hスパイク発生
    修正: can_update_rx_filters()で無効チャンネルでもマスク0x7FFを維持
2026-02-11 fix: add variant ID verification to prevent firmware mix-up (#105)
    - Added variant_id.h auto-generation in build_variants.ps1
    - Embedded VARIANT:awXXX string in firmware binary
    - Added build-time verification to ensure binary matches expected variant
    - Updated release-manifest.json with correct checksums
    This prevents the issue where the wrong firmware variant
    gets uploaded to the wrong file name.
2026-02-12 fix(android): ギア比設定のAndroid-Windows間互換性バグを修正 + ホストアプリv1.0.1
    * fix(android): ギア比設定のAndroid-Windows間互換性バグを修正
    - ギア比を1000倍の整数値で送信するように修正（ファームウェアはatoi()で整数パース）
    - SimulatorServiceのギア比内部表現を整数に統一
    - saveParameters()後にexitコマンドを送信
    - loadParameters()の先頭で空文字送信してパラメータモードに入るように修正
    * release: v1.0.1ホストアプリのAbout画面バージョン表示を動的取得に変更
2026-02-12 CAN車速受信時の車速表示不備, CAN車速ベースのオドメータ積算ロジック追加(自動切り替え) (#109)
    * -ホスト側CANセッティングでEnable/Disableが操作できない不備修正
    -CANでSPEED設定時はCAN値を車速表示するように変更
    * fix(HostApp): Correct Default button binding to ResetDefaultCommand
    Fixes regression that would cause Default button to not work after merge
    * fix: CAN Settings表示の重複とギア比デフォルト値を修正
    - Items.Refresh()を削除（TwoWayバインディングと競合していた）
2026-02-13 fix: makefile.defs aw/ subdir.mk二重インクルード修正 + リリースアセット更新
    - makefile.defsのfilterガードパス修正 (./aw/ -> aw/) により
    subdir.mkの二重インクルードを防止
    - aw001ファームウェアをtrip_resetバグ修正込みで再ビルド
    - release-manifest.json aw001 SHA256更新
2026-02-13 fix: makefile.defs削除 + build_variants.ps1にmakefile検証追加 (#113)
    - makefile.defsを削除: ソースロケーション設定の復元が正しい対策であり不要
    - build_variants.ps1にmakefileのaw/インクルード行検証を追加
    → ソースロケーション欠落時にビルド前にエラーと対処法を表示
2026-03-06 fix: .gitmodulesにlvglサブモジュールを追加 Phase2実装まで動作確認
2026-03-08 feat: EPS駆動用タコ・車速パルス出力機能を追加 （2dc85e1のコミット内容をマージ）
2026-03-09 タコメータ駆動範囲の定数設定ミス修正 (可動域260deg -> 270deg)
2026-03-12 fix: AppWizardヘッダサイズを12→16バイトに修正 (lnk.bmp画像乱れ対策) (#118)
    * fix: AppWizardヘッダサイズを12→16バイトに修正 (lnk.bmp画像乱れ対策)
    AppWizard GUI_BITMAP_STREAM形式のヘッダは16バイト（NumColors + NumTransPixels
    フィールドを含む）だが、コンバーターが12バイトと誤認していたため、
    ピクセルデータが4バイトずれて書き込まれていた。
    mtc.bmpは先頭ピクセルが黒(0x0000)のためNumColors=0となり偶然正常表示されたが、
    lnk.bmpは先頭ピクセルが非黒のためNumColorsが非ゼロに解釈され画像が乱れていた。
2026-03-23 feat: migrate UI from SquareLine Studio to EEZ Studio (LVGL native)
2026-03-24 fix: linker_script.ldからGUIConf.o関連の除外ルールを削除
2026-03-24 docs: SEGGER/emWin/AppWizard参照をLVGLに更新、qe_emwin_config.h削除
    - qe_emwin_config.h: 未参照のため削除
    - README.md: グラフィック SEGGER emWin → LVGL 8.3 (EEZ Studio)
    - THIRD_PARTY_NOTICES.md: SEGGER emWinセクション削除
    - Firmware/README.md: emWin code generation/AppWizardバリアントセクション削除
    - Firmware/docs/PARAM_CONSOLE.md: emWin→LVGL (排他制御、動作モード表)
    - ソースコメント: emWin参照をLVGL/GLCDCに置換 (pulse_out.c, lv_port_disp.c等)
2026-03-25 chore: EEZプロジェクトをgit管理対象に追加
    Firmware/eez/をgitignoreから除外し、プロジェクトファイル・画像・フォントを追跡対象にした。
    ui-stateファイルは引き続きignore。
2026-03-26 docs: EEZデザイン切替システムのドキュメント追加
2026-04-05 fix(eez003): EEZ Studio再生成 + 不要画像削除 + LVGLヒープ増量
    - EEZ Studioでscreens.c/h等を再生成（Prodrive用レイアウト反映）
    - screens.c: LV_LABEL_LONG_undefined→LV_LABEL_LONG_CLIP, get_var_0→get_var_rpm
    - 不要なeez001画像16ファイル削除（ROM 298KBオーバーフロー解消）
    - images.c/h: 27→11画像に整理（screens.cが参照する画像のみ）
    - lv_conf.h: LV_MEM_SIZE 32KB→48KB（ウィジェット数43→153対応）
    - sync_ui_subdir_mk.ps1追加

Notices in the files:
parts and their libraries:
COPYRIGHT: Copyright (C) 2024 Ultra Librarian. All rights reserved.
